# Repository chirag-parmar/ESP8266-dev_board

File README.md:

# ESP8266 Development Board
ESP8266 Development Board for easy porgramming of ESP8266-01. This board goes atop an Arduino-UNO R3 as a shield.

*The schematics and board files require ESP8266 eagle libraries and sparkfun eagle libraries.*

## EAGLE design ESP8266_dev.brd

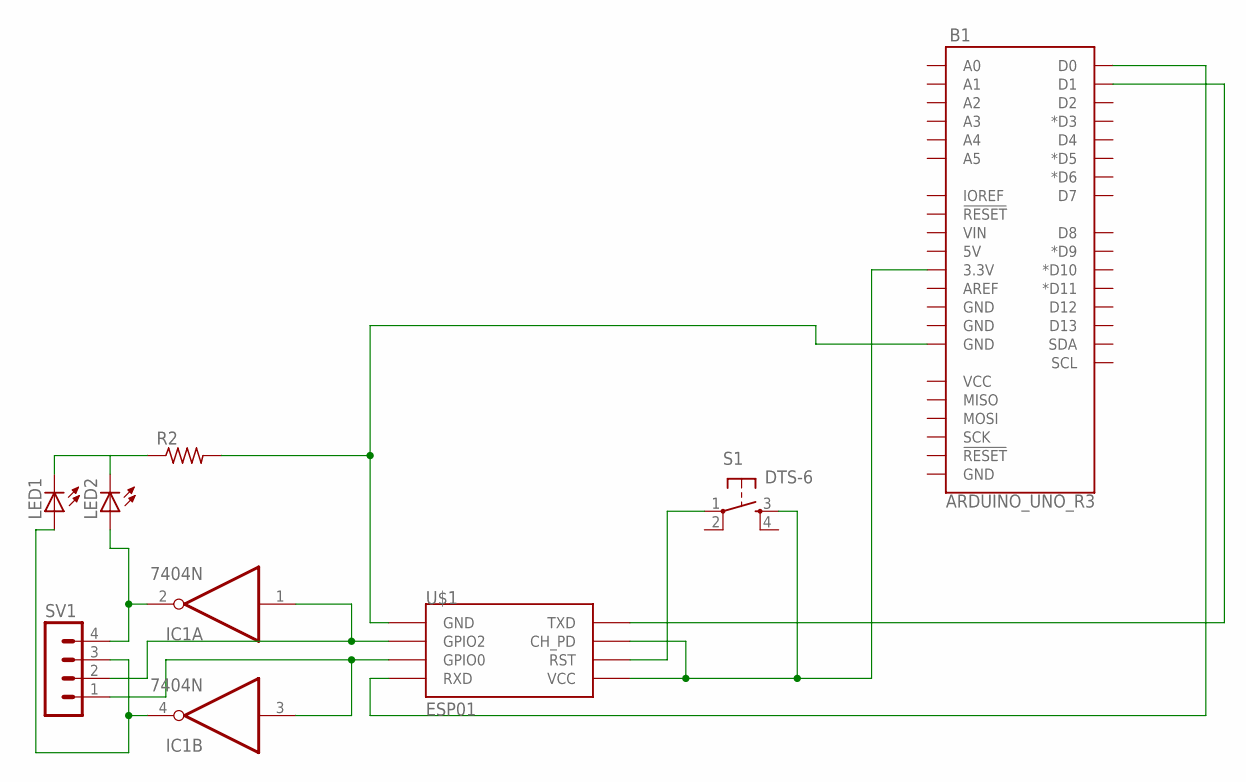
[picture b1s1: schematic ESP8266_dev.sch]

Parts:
B1: ARDUINO_UNO_R3; ARDUINO_R3
IC1: 7404N; DIL14
LED1, LED2: LED3MM
R2: R-US_0207/15; 0207/15
S1: DTS-6
SV1: MA04-1
U$1: ESP01

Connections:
GND: IC1.7 (GND)
unnamed: B1.3.3V, S1.3, U$1.CH_PD, U$1.VCC
unnamed: S1.1, U$1.RST
unnamed: B1.D1, U$1.TX (TXD)
unnamed: B1.D0, U$1.RX (RXD)
unnamed: B1.GND@2 (GND), R2.2, U$1.GND
unnamed: IC1.1 (I), SV1.2, U$1.GPIO2
unnamed: IC1.3 (I), SV1.1, U$1.GPIO0
unnamed: IC1.4 (O), LED1.A, SV1.3
unnamed: IC1.2 (O), LED2.A, SV1.4
unnamed: LED1.K (C), LED2.K (C), R2.1
VCC: IC1.14 (VCC)

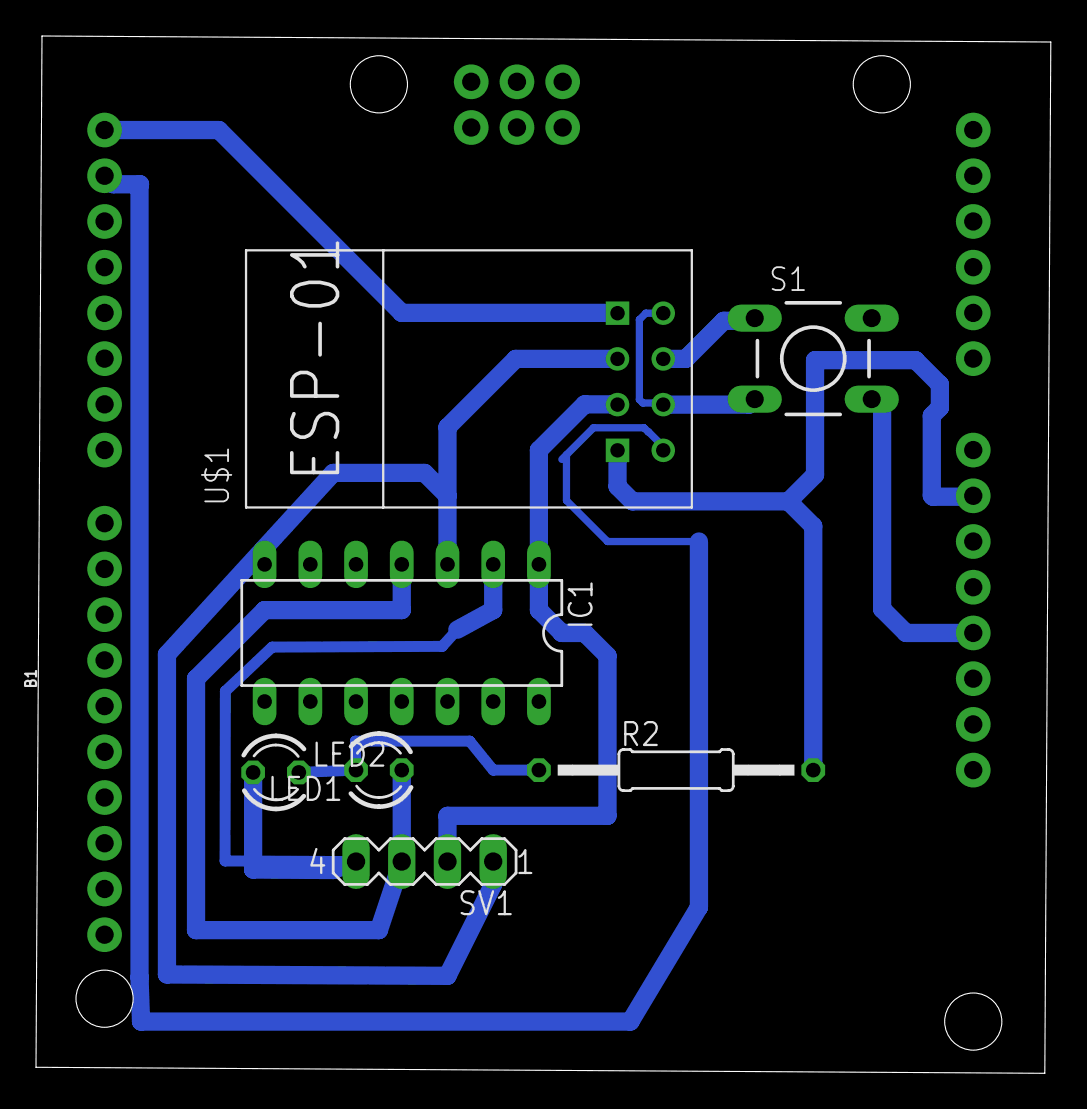
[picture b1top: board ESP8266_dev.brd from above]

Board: 2 copper layers, 56.4 x 57.6 mm, 8 parts (0 on the bottom side), 10 nets.

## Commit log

2017-03-25 Added design images

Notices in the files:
parts and their libraries:
SparkFun-Boards: Licensing: Creative Commons ShareAlike 4.0 International - https://creativecommons.org/licenses/by-sa/4.0
